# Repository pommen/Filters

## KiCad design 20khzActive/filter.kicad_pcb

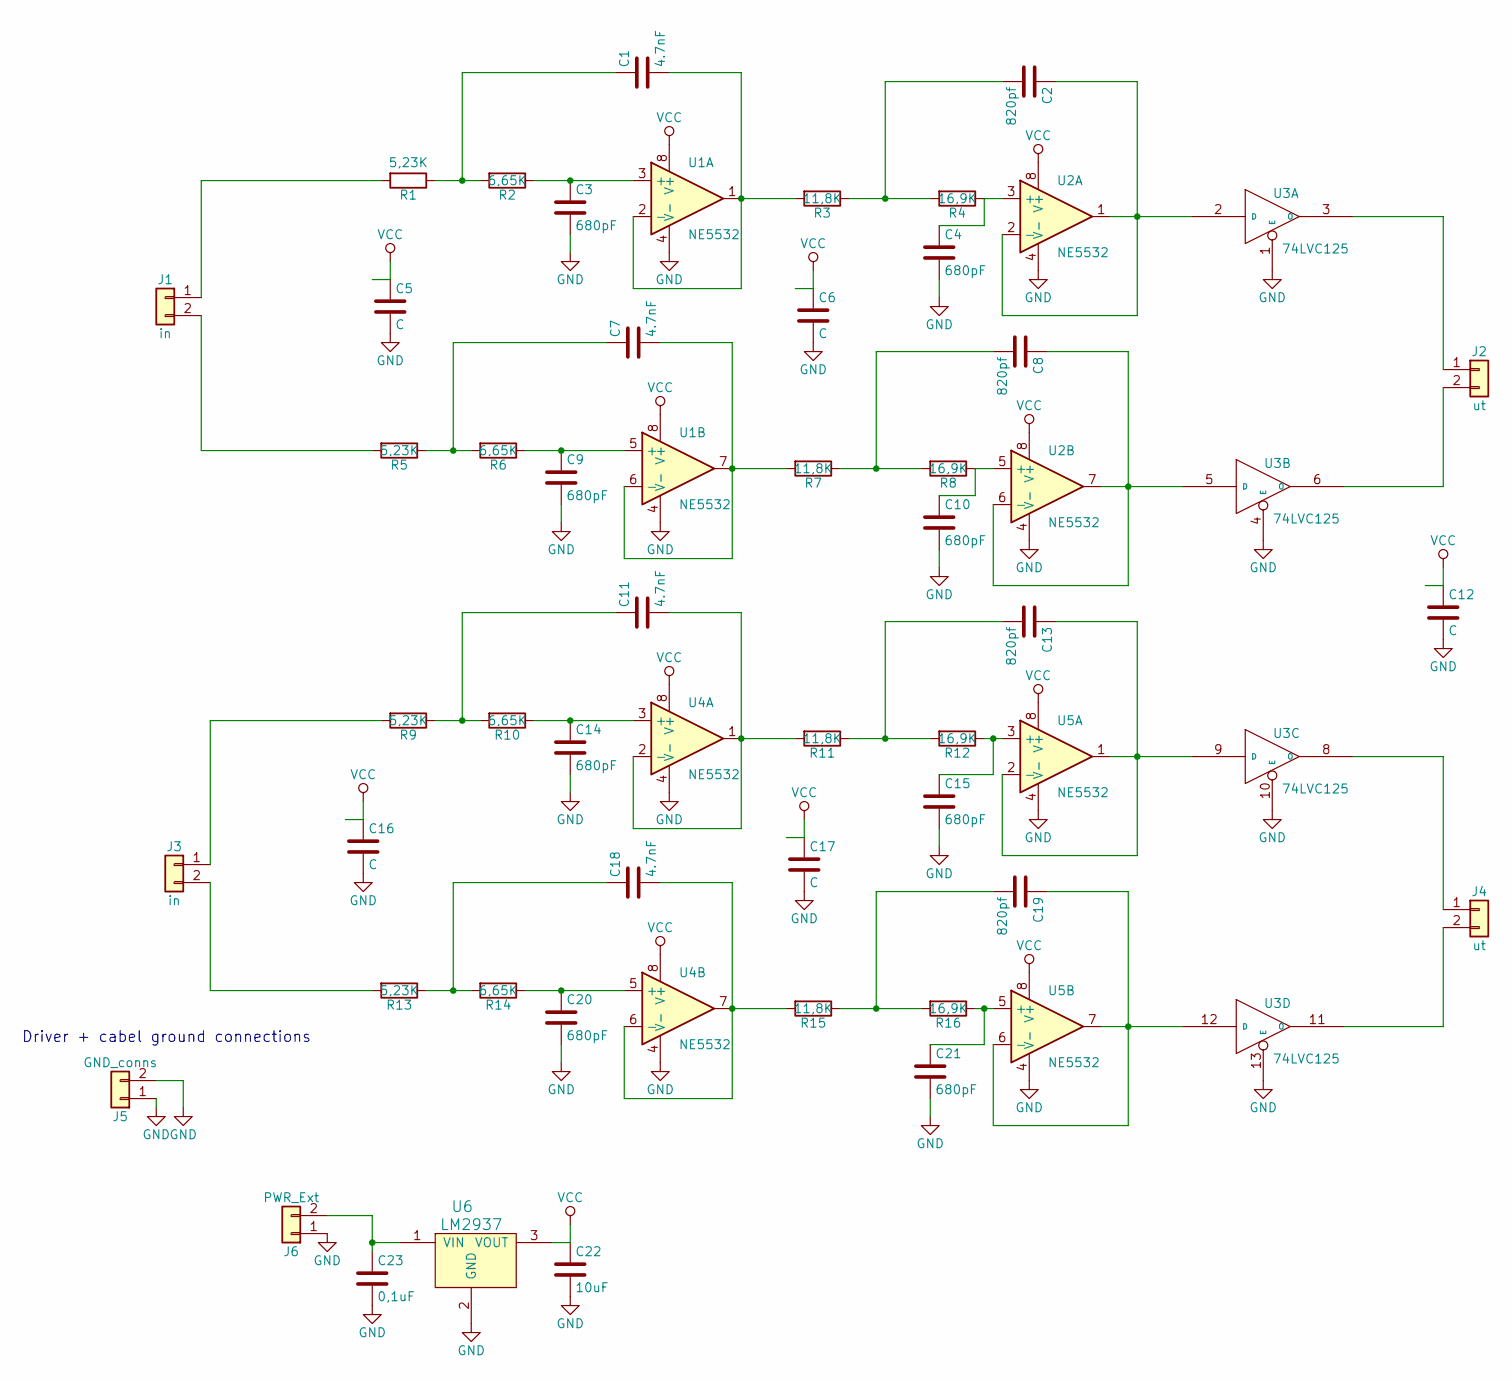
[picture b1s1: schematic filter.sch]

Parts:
C1, C7, C11, C18: 4.7nF; C_0805_HandSoldering
C2, C8, C13, C19: 820pf; C_0805_HandSoldering
C3, C4, C9, C10, C14, C15, C20, C21: 680pF; C_0805_HandSoldering
C5, C6, C12, C16, C17: C; C_0805_HandSoldering
C22: 10uF; C_0805_HandSoldering
C23: 0,1uF; C_0805_HandSoldering
J1, J3: in; JUMPER_5MM
J2, J4: ut; JUMPER_5MM
J5: GND_conns; TerminalBlock_bornier-2_P5.08mm
J6: PWR_Ext; TerminalBlock_bornier-2_P5.08mm
R1, R5, R9, R13: 5,23K; R_0805_HandSoldering
R2, R6, R10, R14: 6,65K; R_0805_HandSoldering
R3, R7, R11, R15: 11,8K; R_0805_HandSoldering
R4, R8, R12, R16: 16,9K; R_0805_HandSoldering
U1, U2, U4, U5: NE5532; SOIC-8_3.9x4.9mm_Pitch1.27mm
U3: 74LVC125; SOIC-14_3.9x8.7mm_Pitch1.27mm
U6: LM2937; SOT-223-3_TabPin2

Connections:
GND: C3.2, C4.2, C5.2, C6.2, C9.2, C10.2, C12.2, C14.2, C15.2, C16.2, C17.2, C20.2, C21.2, C22.2, C23.2, J5.1, J5.2, J6.1, U1.4 (V-), U2.4 (V-), U3.1 (E), U3.4 (E), U3.7 (GND), U3.10 (E), U3.13 (E), U4.4 (V-), U5.4 (V-), U6.2 (GND)
unnamed: C1.1, R1.1, R2.2
unnamed: C1.2, R3.2, U1.1, U1.2 (-)
unnamed: C2.1, U2.1, U2.2 (-), U3.2 (D)
unnamed: C2.2, R3.1, R4.2
unnamed: C3.1, R2.1, U1.3 (+)
unnamed: C4.1, R4.1, U2.3 (+)
unnamed: C7.1, R5.1, R6.2
unnamed: C7.2, R7.2, U1.6 (-), U1.7
unnamed: C8.1, U2.6 (-), U2.7, U3.5 (D)
unnamed: C8.2, R7.1, R8.2
unnamed: C9.1, R6.1, U1.5 (+)
unnamed: C10.1, R8.1, U2.5 (+)
unnamed: C11.1, R9.1, R10.2
unnamed: C11.2, R11.2, U4.1, U4.2 (-)
unnamed: C13.1, U3.9 (D), U5.1, U5.2 (-)
unnamed: C13.2, R11.1, R12.2
unnamed: C14.1, R10.1, U4.3 (+)
unnamed: C15.1, R12.1, U5.3 (+)
unnamed: C18.1, R13.1, R14.2
unnamed: C18.2, R15.2, U4.6 (-), U4.7
unnamed: C19.1, U3.12 (D), U5.6 (-), U5.7
unnamed: C19.2, R15.1, R16.2
unnamed: C20.1, R14.1, U4.5 (+)
unnamed: C21.1, R16.1, U5.5 (+)
unnamed: C23.1, J6.2, U6.1 (VIN)
unnamed: J1.1, R1.2
unnamed: J1.2, R5.2
unnamed: J2.1, U3.3 (O)
unnamed: J2.2, U3.6 (O)
unnamed: J3.1, R9.2
unnamed: J3.2, R13.2
unnamed: J4.1, U3.8 (O)
unnamed: J4.2, U3.11 (O)
VCC: C5.1, C6.1, C12.1, C16.1, C17.1, C22.1, U1.8 (V+), U2.8 (V+), U3.14 (VCC), U4.8 (V+), U5.8 (V+), U6.3 (VOUT)

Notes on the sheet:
Driver + cabel ground connections

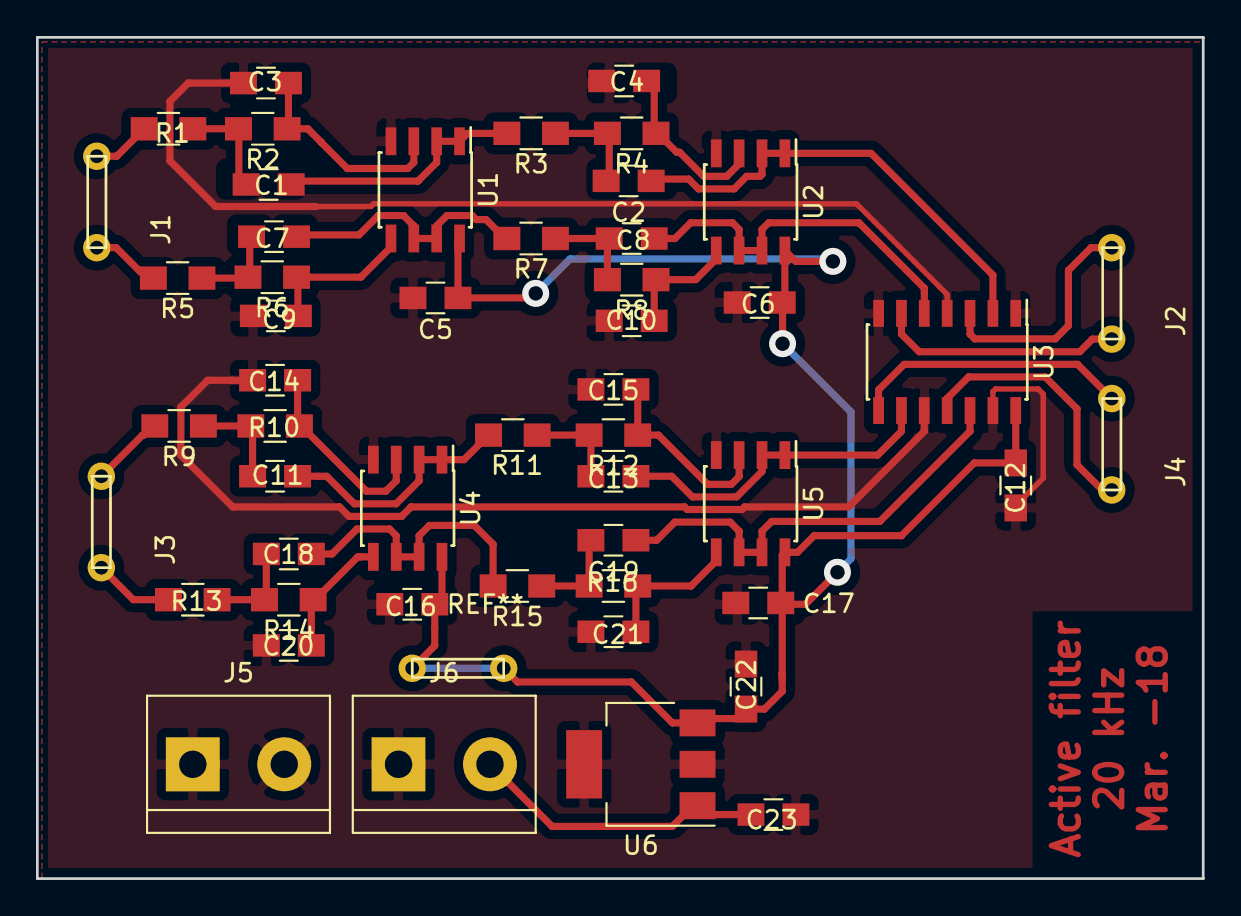
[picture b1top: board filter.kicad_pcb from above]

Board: 2 copper layers, 64.8 x 46.7 mm, 51 parts (0 on the bottom side), 35 nets.

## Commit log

2018-03-06 First
2018-08-12 exported to 5.0
